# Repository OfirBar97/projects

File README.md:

# Embedded Hardware & Software Engineering Portfolio

👋 Hi there! I'm Ofir Bar, an Electrical Engineer passionate about embedded systems, hardware design, and firmware development. 
This repository serves as a portfolio of my projects, experiments, and learning journey in the world of embedded engineering.

---

## 🚀 About Me

- **Background**: Electrical Engineer with knowledge in {Circuit design, Low level Programming, MATLAB, Lab Equipment, Computer Architecture, Deep Learning, Machine Learning, Image processing Libraries, etc}.
- **Focus**: Focused on embedded systems and signal and image processing, combining hardware and software to build efficient, real-world solutions.
- **Goal**: To create innovative, reliable, and scalable embedded systems that solve real-world problems.

## 🛠️ Tools & Technologies

Here are the tools and technologies I frequently use:

  **Keeping it short and to the point**
  
| **Category**        | **Tools/Technologies**                                                          |
|---------------------|---------------------------------------------------------------------------------|
| **Hardware Design** | KiCad, Multisim, OrCAD                                         |
| **Microcontrollers**| Arduino, STM32, Rasberry Pi, FPGA                                                     |
| **Programming**     | Embedded C/C++, Python, MATLAB, Verilog, VHDL                                            |
| **Communication Protocols**     | I2C, SPI, UART                                          |
| **Simulation**      | LTspice, MATLAB/Simulink                                                        |
| **Lab Tools**       | Logic Analyzer, Oscilloscope, Signal Generator, Spectrum analyzer, Multimeters  |
| **Advanced in**     | Deep Learning, Machine Learning, Signal & Image processing                      |
| **Libraries**       | Pandas, NumPy, Matploitlib, TensorFlow, Keras, SickitLearn, OpenCV              |
| **Version Control** | Git, GitHub                                                             |

---

## 🛠️ Projects

Here are some of the projects I've worked on:

### 1. **Algorithm for Noise Filtering and Information Extraction from Fingerprints**
   - **Description**: An algorithm I developed to extract fingerprint minutiae points for classifying human morphological attributes.
   - **Features**: Fingerprint scanner analysis and decoding, sensor data logging, and security appliance integration.
   - **Tech Stack**: MATLAB.
   - [Link to Project](https://github.com/OfirBar97/projects/blob/main/Fingerprint%20Recognition%20System/Project%20Poster.pdf)
     
### 2. **Digital Communication - QPSK Modulation**
   - **Description**: a Quadrature Phase Shift Keying (QPSK) Modulation, Transmitting Data and recieving Data with and without noise simulations.
   - **Features**: Wireless Communication – Found in LTE, 5G, Wi-Fi (IEEE 802.11), and Bluetooth standards for high-speed data transmission.
   - **Tech Stack**: MATLAB.
   - [Link to Project](https://github.com/OfirBar97/projects/blob/main/QPSK.pdf)

### 3. **Designed RAM Module for FPGA**
   - **Description**: RAM memory unit and reset feature module and test benches, designed with Verilog
   - **Features**: The operating system (OS) itself uses RAM to manage system processes, handle user inputs, and run background services.
   - **Tech Stack**: Verilog, Xilinx Vivado, FPGA.
   - [Link to Project](https://github.com/OfirBar97/projects/blob/main/RAM%20module%20for%20FPGA/SRAM_Waveform.png)

---

## 📚 Learning Resources

Here are some resources that have helped me in my journey:
- **Bachelor of Applied Science B.Sc - Electrical and Electronics Engineer**
        <sub>SCE - College of Engineering, Be'er Sheva</sub>
- **SoC 101 Computer Architecture - Prof. Adi Teman**
        <sub>Bar Ilan University, Ramat gan</sub>
- **Linux Cyber Security and Cisco networks managment**
        <sub>HackerU Academy, Ramat Gan</sub>

- **Online Courses & Cerifications**:
  - 'Design an STM32-based prototype from scratch in KiCad V6' - Phil's Lab
  - 'Getting started with Deep Learning' - NVIDIA
  - 'Verilog for FPGA Development' - Prof. Eduardo Corpeño
  - 'Fundamentals of Accelerated Computing with CUDA Python' - NVIDIA
  - 'Machine learning in Python with scikit-learn' - France Université Numérique
  - '100 Days of Code: The Complete Python Pro Bootcamp' - Dr. Angela Yu
 
- **Books**:
  - "Digital Logic Design Using Verilog" by Vaibbhav Taraate
  - "Making Embedded Systems" by Elecia White
  - "The Art of Electronics" by Horowitz and Hill  
- **Communities**:
  - [Hardreset Podcast](https://open.spotify.com/show/2jVk9zuhcDS8KAavPNyTDu)
  - [r/embedded on Reddit](https://www.reddit.com/r/embedded/)

---

## 🤝 Let's Connect!

I'm always open to collaborations, discussions, and feedback. Feel free to reach out to me:

- **Email**: [Ofirbar97@gmail.com](Ofirbar97@gmail.com)
- **LinkedIn**: [LinkedIn](https://www.linkedin.com/in/ofir-bar-97see/)

---

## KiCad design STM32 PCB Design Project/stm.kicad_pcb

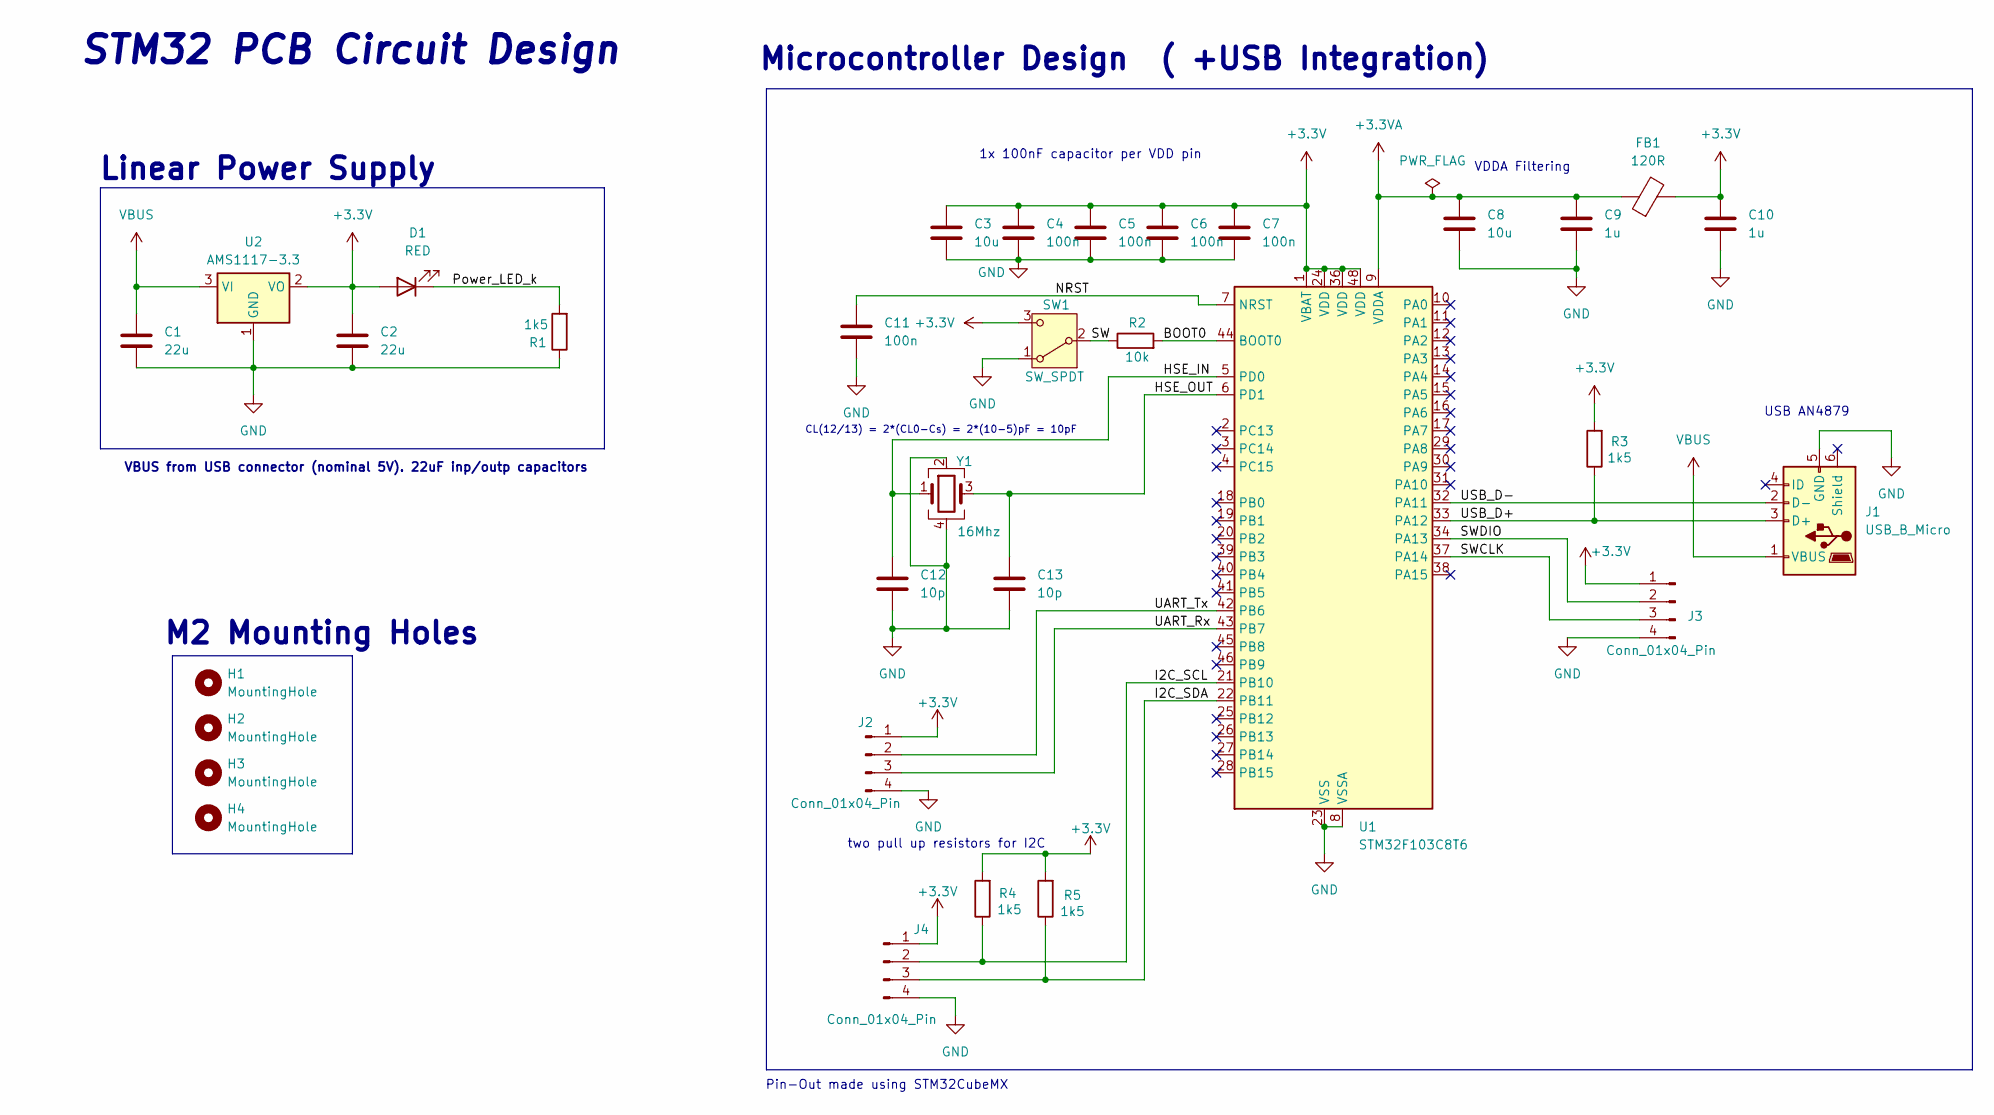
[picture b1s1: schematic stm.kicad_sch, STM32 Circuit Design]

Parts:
C1, C2: 22u; C_0402_1005Metric
C3, C8: 10u; C_0402_1005Metric
C4, C7, C11: 100n; C_0402_1005Metric
C5, C6: 100n; C_0201_0603Metric
C9, C10: 1u; C_0402_1005Metric
C12: 10p; C_0805_2012Metric
C13: 10p; C_0402_1005Metric
D1: RED; LED_0201_0603Metric
FB1: 120R; L_0603_1608Metric
H1, H2, H3, H4: MountingHole; MountingHole_2.2mm_M2
J1: USB_B_Micro; USB_Micro-B_Wuerth_629105150521
J2, J3, J4: Conn_01x04_Pin; PinHeader_1x04_P2.54mm_Vertical
R1, R3, R4, R5: 1k5; R_0402_1005Metric
R2: 10k; R_0402_1005Metric
SW1: SW_SPDT; SW_E-Switch_EG1224_SPDT_Angled
U1: STM32F103C8T6; LQFP-48_7x7mm_P0.5mm
U2: AMS1117-3.3; SOT-223-3_TabPin2
Y1: 16Mhz; Crystal_SMD_3225-4Pin_3.2x2.5mm

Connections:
+3.3V: C2.1, C3.1, C4.1, C5.1, C6.1, C7.1, C10.1, D1.2 (A), FB1.2, J2.1, J3.1, J4.1, R3.2, R4.2, R5.2, SW1.3 (C), U1.1 (VBAT), U1.24 (VDD), U1.36 (VDD), U1.48 (VDD), U2.2 (VO)
+3.3VA: C8.1, C9.1, FB1.1, U1.9 (VDDA)
/BOOT0: R2.2, U1.44 (BOOT0)
/HSE_IN: C12.1, U1.5 (PD0), Y1.1
/HSE_OUT: C13.1, U1.6 (PD1), Y1.3
/I2C_SCL: J4.2, R4.1, U1.21 (PB10)
/I2C_SDA: J4.3, R5.1, U1.22 (PB11)
/NRST: C11.1, U1.7 (NRST)
/Power_LED_k: D1.1 (K), R1.2
/SW: R2.1, SW1.2 (B)
/SWCLK: J3.3, U1.37 (PA14)
/SWDIO: J3.2, U1.34 (PA13)
/UART_Rx: J2.3, U1.43 (PB7)
/UART_Tx: J2.2, U1.42 (PB6)
/USB_D+: J1.3 (D+), R3.1, U1.33 (PA12)
/USB_D-: J1.2 (D-), U1.32 (PA11)
GND: C1.2, C2.2, C3.2, C4.2, C5.2, C6.2, C7.2, C8.2, C9.2, C10.2, C11.2, C12.2, C13.2, J1.5 (GND), J2.4, J3.4, J4.4, R1.1, SW1.1 (A), U1.8 (VSSA), U1.23 (VSS), U1.35 (VSS), U1.47 (VSS), U2.1 (GND), Y1.2, Y1.4
VBUS: C1.1, J1.1 (VBUS), U2.3 (VI)

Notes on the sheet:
Microcontroller Design ( +USB Integration)
STM32 PCB Circuit Design
USB AN4879
1x 100nF capacitor per VDD pin
VDDA Filtering
M2 Mounting Holes
CL(12/13) = 2*(CL0-Cs) = 2*(10-5)pF = 10pF
Linear Power Supply
Pin-Out made using STM32CubeMX
VBUS from USB connector (nominal 5V). 22uF inp/outp capacitors
two pull up resistors for I2C

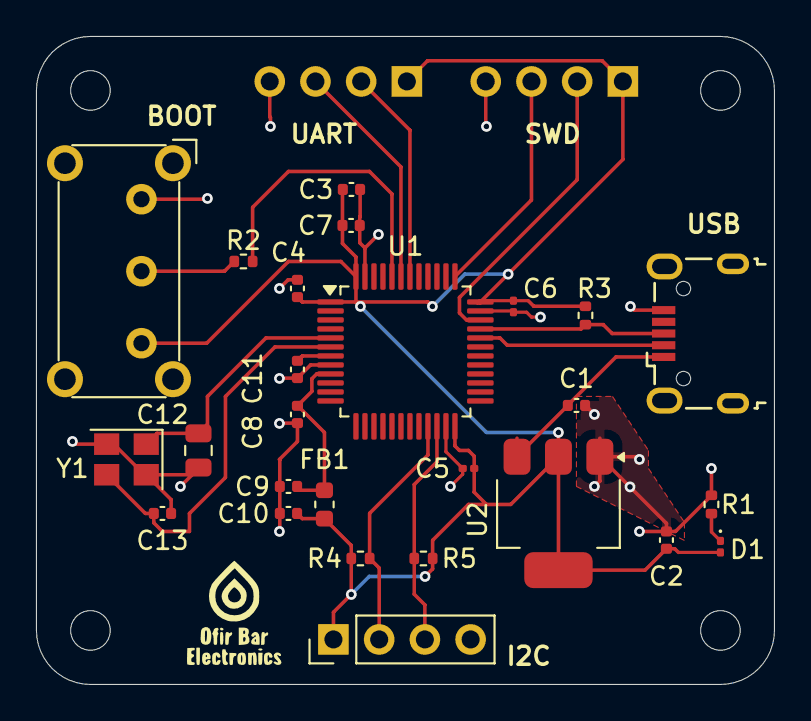
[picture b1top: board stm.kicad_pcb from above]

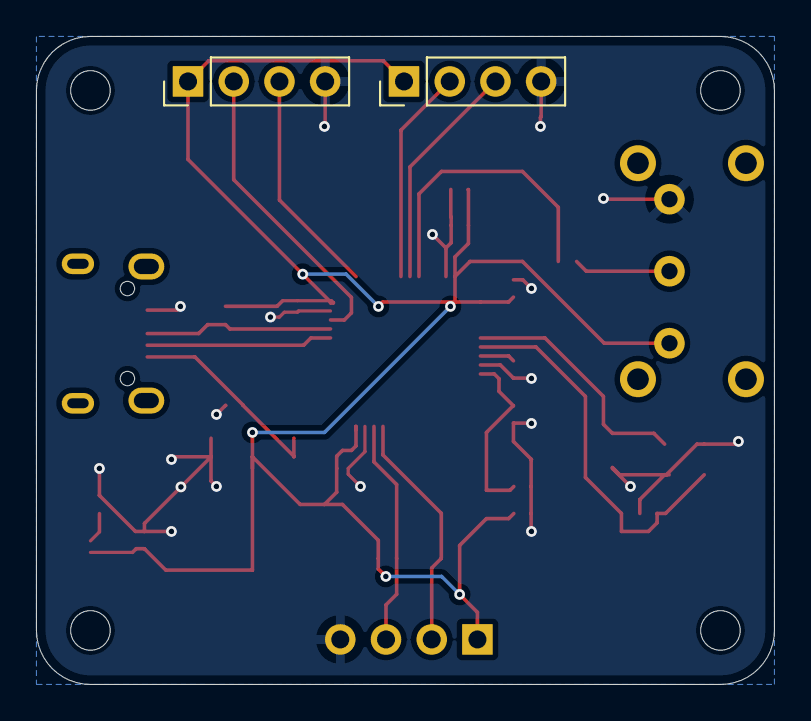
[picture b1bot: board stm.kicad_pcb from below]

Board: 2 copper layers, 41.0 x 36.0 mm, 32 parts (2 on the bottom side), 18 nets.

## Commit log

2025-02-04 README.md
2025-02-05 Create Fingerprint Extraction Algorithm
2025-02-05 Update Fingerprint Extraction Algorithm
2025-02-05 Add files via upload
    Run MATLAB Algorithm with Finger_Print_Sample.bmp as Input
2025-02-05 SRAM Verilog exercise
2025-02-05 MATLAB Fingerprint Algorithm
2025-03-23 Updated Minutiae_Extraction_Algorithm.m
2025-03-23 MATLAB Fingerprint Extraction points -Product Picture
2025-03-23 MATLAB fingerprint extraction ridges & bifurcations
2025-06-11 Rename QPSK.pdf to QPSK Modulation.pdf
2025-06-11 Create Fingerprint Recognition System
2025-06-11 Source Code
2025-06-11 Create Code and Simulation
